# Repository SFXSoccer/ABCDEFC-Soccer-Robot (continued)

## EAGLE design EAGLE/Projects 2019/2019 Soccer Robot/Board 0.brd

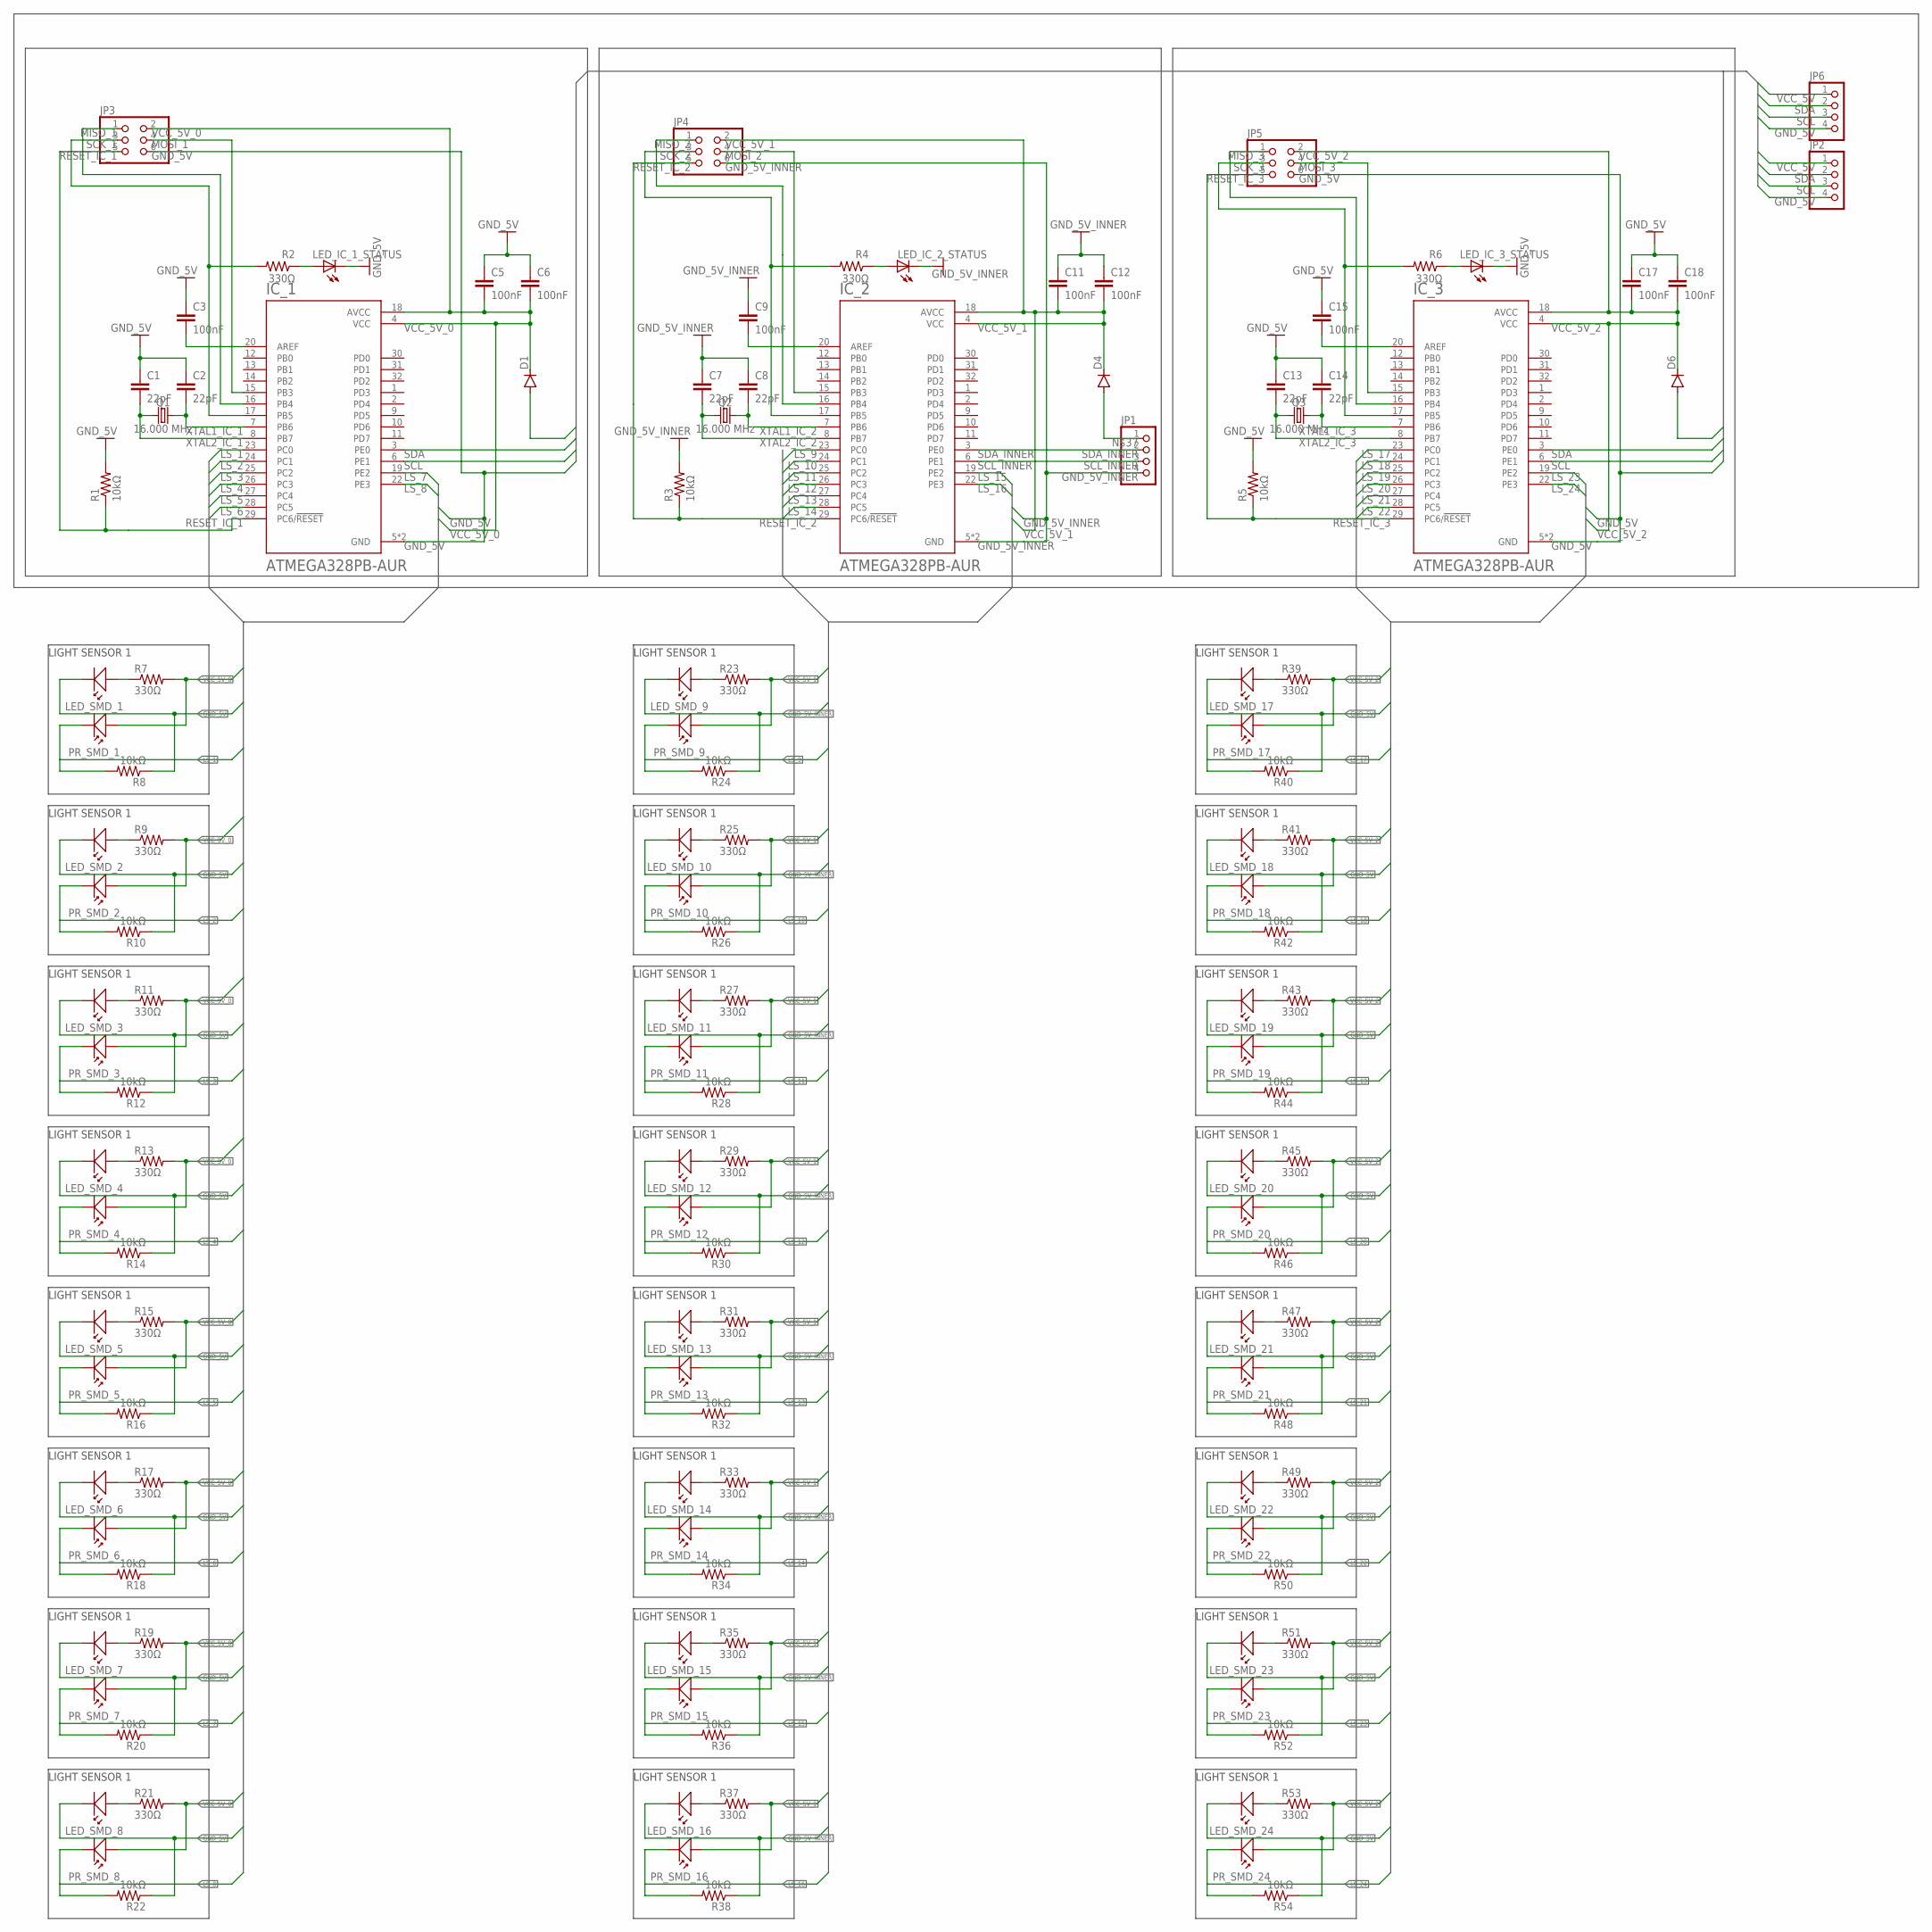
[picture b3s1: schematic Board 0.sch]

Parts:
C1, C2, C7, C8, C13, C14: 22pF; C1206
C3, C5, C6, C9, C11, C12, C15, C17, C18: 100nF; C1206
D1, D4, D6: DIODE-SOD123; SOD123
IC_1, IC_2, IC_3: ATMEGA328PB-AUR; QFP80P900X900X120-32N
JP1, JP2, JP6: PINHD-1X4_2.54-SMD; 1X04SMD
JP3, JP4, JP5: PINHD-2X3_2.54-SMD; 2X03SMD
LED_IC_1_STATUS, LED_IC_2_STATUS, LED_IC_3_STATUS: LEDP-LCC-2; P-LCC-2
LED_SMD_1, LED_SMD_2, LED_SMD_3, LED_SMD_4, LED_SMD_5, LED_SMD_6, LED_SMD_7, LED_SMD_8, LED_SMD_9, LED_SMD_10, LED_SMD_11, LED_SMD_12, LED_SMD_13, LED_SMD_14, LED_SMD_15, LED_SMD_16, LED_SMD_17, LED_SMD_18, LED_SMD_19, LED_SMD_20, LED_SMD_21, LED_SMD_22, LED_SMD_23, LED_SMD_24: SMD_LED_3MM
PR_SMD_1, PR_SMD_2, PR_SMD_3, PR_SMD_4, PR_SMD_5, PR_SMD_6, PR_SMD_7, PR_SMD_8, PR_SMD_9, PR_SMD_10, PR_SMD_11, PR_SMD_12, PR_SMD_13, PR_SMD_14, PR_SMD_15, PR_SMD_16, PR_SMD_17, PR_SMD_18, PR_SMD_19, PR_SMD_20, PR_SMD_21, PR_SMD_22, PR_SMD_23, PR_SMD_24: SMD_PHOTORESISTOR_5MM
Q1, Q2, Q3: 16.000 MHz; CRYSTAL-SMD-5X3.2-4PAD
R1, R3, R5, R8, R10, R12, R14, R16, R18, R20, R22, R24, R26, R28, R30, R32, R34, R36, R38, R40, R42, R44, R46, R48, R50, R52, R54: 10kΩ; R1206
R2, R4, R6, R7, R9, R11, R13, R15, R17, R19, R21, R23, R25, R27, R29, R31, R33, R35, R37, R39, R41, R43, R45, R47, R49, R51, R53: 330Ω; R1206

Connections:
GND_5V: C1.1, C2.1, C3.1, C5.1, C6.1, C13.1, C14.1, C15.1, C17.1, C18.1, IC_1.5 (GND), IC_1.21 (GND), IC_3.5 (GND), IC_3.21 (GND), JP2.4, JP3.6, JP5.6, JP6.4, LED_IC_1_STATUS.C, LED_IC_3_STATUS.C, LED_SMD_1.GND, LED_SMD_2.GND, LED_SMD_3.GND, LED_SMD_4.GND, LED_SMD_5.GND, LED_SMD_6.GND, LED_SMD_7.GND, LED_SMD_8.GND, LED_SMD_17.GND, LED_SMD_18.GND, LED_SMD_19.GND, LED_SMD_20.GND, LED_SMD_21.GND, LED_SMD_22.GND, LED_SMD_23.GND, LED_SMD_24.GND, R1.2, R5.2, R8.1, R10.1, R12.1, R14.1, R16.1, R18.1, R20.1, R22.1, R40.1, R42.1, R44.1, R46.1, R48.1, R50.1, R52.1, R54.1
GND_5V_INNER: C7.1, C8.1, C9.1, C11.1, C12.1, IC_2.5 (GND), IC_2.21 (GND), JP1.4, JP4.6, LED_IC_2_STATUS.C, LED_SMD_9.GND, LED_SMD_10.GND, LED_SMD_11.GND, LED_SMD_12.GND, LED_SMD_13.GND, LED_SMD_14.GND, LED_SMD_15.GND, LED_SMD_16.GND, R3.2, R24.1, R26.1, R28.1, R30.1, R32.1, R34.1, R36.1, R38.1
LS_1: IC_1.23 (PC0), PR_SMD_1.GND, R8.2
LS_2: IC_1.24 (PC1), PR_SMD_2.GND, R10.2
LS_3: IC_1.25 (PC2), PR_SMD_3.GND, R12.2
LS_4: IC_1.26 (PC3), PR_SMD_4.GND, R14.2
LS_5: IC_1.27 (PC4), PR_SMD_5.GND, R16.2
LS_6: IC_1.28 (PC5), PR_SMD_6.GND, R18.2
LS_7: IC_1.19 (PE2), PR_SMD_7.GND, R20.2
LS_8: IC_1.22 (PE3), PR_SMD_8.GND, R22.2
LS_9: IC_2.23 (PC0), PR_SMD_9.GND, R24.2
LS_10: IC_2.24 (PC1), PR_SMD_10.GND, R26.2
LS_11: IC_2.25 (PC2), PR_SMD_11.GND, R28.2
LS_12: IC_2.26 (PC3), PR_SMD_12.GND, R30.2
LS_13: IC_2.27 (PC4), PR_SMD_13.GND, R32.2
LS_14: IC_2.28 (PC5), PR_SMD_14.GND, R34.2
LS_15: IC_2.19 (PE2), PR_SMD_15.GND, R36.2
LS_16: IC_2.22 (PE3), PR_SMD_16.GND, R38.2
LS_17: IC_3.23 (PC0), PR_SMD_17.GND, R40.2
LS_18: IC_3.24 (PC1), PR_SMD_18.GND, R42.2
LS_19: IC_3.25 (PC2), PR_SMD_19.GND, R44.2
LS_20: IC_3.26 (PC3), PR_SMD_20.GND, R46.2
LS_21: IC_3.27 (PC4), PR_SMD_21.GND, R48.2
LS_22: IC_3.28 (PC5), PR_SMD_22.GND, R50.2
LS_23: IC_3.19 (PE2), PR_SMD_23.GND, R52.2
LS_24: IC_3.22 (PE3), PR_SMD_24.GND, R54.2
MISO_1: IC_1.16 (PB4), JP3.1
MISO_2: IC_2.16 (PB4), JP4.1
MISO_3: IC_3.16 (PB4), JP5.1
MOSI_1: IC_1.15 (PB3), JP3.4
MOSI_2: IC_2.15 (PB3), JP4.4
MOSI_3: IC_3.15 (PB3), JP5.4
unnamed: C3.2, IC_1.20 (AREF)
unnamed: LED_IC_1_STATUS.A, R2.1
unnamed: LED_SMD_2.VIN, R9.1
unnamed: C9.2, IC_2.20 (AREF)
unnamed: LED_IC_2_STATUS.A, R4.1
unnamed: LED_SMD_3.VIN, R11.1
unnamed: LED_SMD_4.VIN, R13.1
unnamed: C15.2, IC_3.20 (AREF)
unnamed: LED_IC_3_STATUS.A, R6.1
unnamed: LED_SMD_1.VIN, R7.1
unnamed: LED_SMD_5.VIN, R15.1
unnamed: LED_SMD_6.VIN, R17.1
unnamed: LED_SMD_7.VIN, R19.1
unnamed: LED_SMD_8.VIN, R21.1
unnamed: LED_SMD_9.VIN, R23.1
unnamed: LED_SMD_10.VIN, R25.1
unnamed: LED_SMD_11.VIN, R27.1
unnamed: LED_SMD_12.VIN, R29.1
unnamed: LED_SMD_13.VIN, R31.1
unnamed: LED_SMD_14.VIN, R33.1
unnamed: LED_SMD_15.VIN, R35.1
unnamed: LED_SMD_16.VIN, R37.1
unnamed: LED_SMD_17.VIN, R39.1
unnamed: LED_SMD_18.VIN, R41.1
unnamed: LED_SMD_19.VIN, R43.1
unnamed: LED_SMD_20.VIN, R45.1
unnamed: LED_SMD_21.VIN, R47.1
unnamed: LED_SMD_22.VIN, R49.1
unnamed: LED_SMD_23.VIN, R51.1
unnamed: LED_SMD_24.VIN, R53.1
unnamed: D4.A, JP1.1
RESET_IC_1: IC_1.29 (PC6/!RESET), JP3.5, R1.1
RESET_IC_2: IC_2.29 (PC6/!RESET), JP4.5, R3.1
RESET_IC_3: IC_3.29 (PC6/!RESET), JP5.5, R5.1
SCK_1: IC_1.17 (PB5), JP3.3, R2.2
SCK_2: IC_2.17 (PB5), JP4.3, R4.2
SCK_3: IC_3.17 (PB5), JP5.3, R6.2
SCL: IC_1.6 (PE1), IC_3.6 (PE1), JP2.3, JP6.3
SCL_INNER: IC_2.6 (PE1), JP1.3
SDA: IC_1.3 (PE0), IC_3.3 (PE0), JP2.2, JP6.2
SDA_INNER: IC_2.3 (PE0), JP1.2
VCC_5V: D1.A, D6.A, JP2.1, JP6.1
VCC_5V_0: C5.2, C6.2, D1.C, IC_1.4 (VCC), IC_1.18 (AVCC), JP3.2, PR_SMD_1.VIN, PR_SMD_2.VIN, PR_SMD_3.VIN, PR_SMD_4.VIN, PR_SMD_5.VIN, PR_SMD_6.VIN, PR_SMD_7.VIN, PR_SMD_8.VIN, R7.2, R9.2, R11.2, R13.2, R15.2, R17.2, R19.2, R21.2
VCC_5V_1: C11.2, C12.2, D4.C, IC_2.4 (VCC), IC_2.18 (AVCC), JP4.2, PR_SMD_9.VIN, PR_SMD_10.VIN, PR_SMD_11.VIN, PR_SMD_12.VIN, PR_SMD_13.VIN, PR_SMD_14.VIN, PR_SMD_15.VIN, PR_SMD_16.VIN, R23.2, R25.2, R27.2, R29.2, R31.2, R33.2, R35.2, R37.2
VCC_5V_2: C17.2, C18.2, D6.C, IC_3.4 (VCC), IC_3.18 (AVCC), JP5.2, PR_SMD_17.VIN, PR_SMD_18.VIN, PR_SMD_19.VIN, PR_SMD_20.VIN, PR_SMD_21.VIN, PR_SMD_22.VIN, PR_SMD_23.VIN, PR_SMD_24.VIN, R39.2, R41.2, R43.2, R45.2, R47.2, R49.2, R51.2, R53.2
XTAL1_IC_1: C2.2, IC_1.7 (PB6), Q1.3 (2)
XTAL1_IC_2: C8.2, IC_2.7 (PB6), Q2.3 (2)
XTAL1_IC_3: C14.2, IC_3.7 (PB6), Q3.3 (2)
XTAL2_IC_1: C1.2, IC_1.8 (PB7), Q1.1
XTAL2_IC_2: C7.2, IC_2.8 (PB7), Q2.1
XTAL2_IC_3: C13.2, IC_3.8 (PB7), Q3.1

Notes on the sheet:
LIGHT SENSOR 1

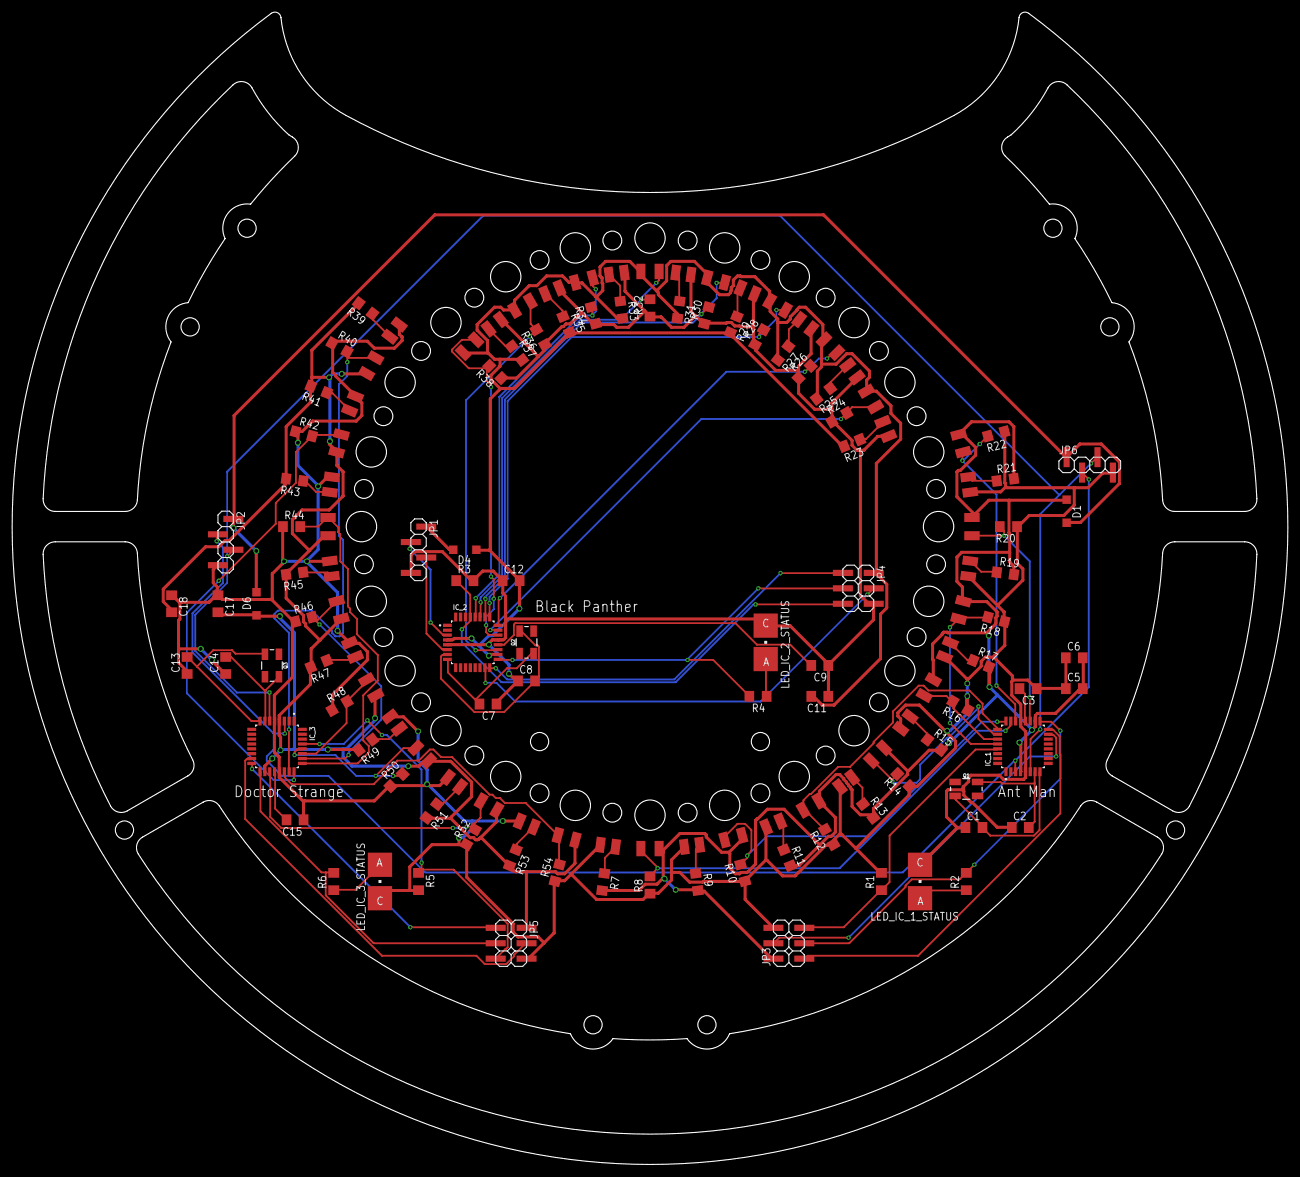
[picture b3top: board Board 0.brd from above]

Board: 2 copper layers, 210.0 x 189.7 mm, 135 parts (0 on the bottom side), 83 nets.

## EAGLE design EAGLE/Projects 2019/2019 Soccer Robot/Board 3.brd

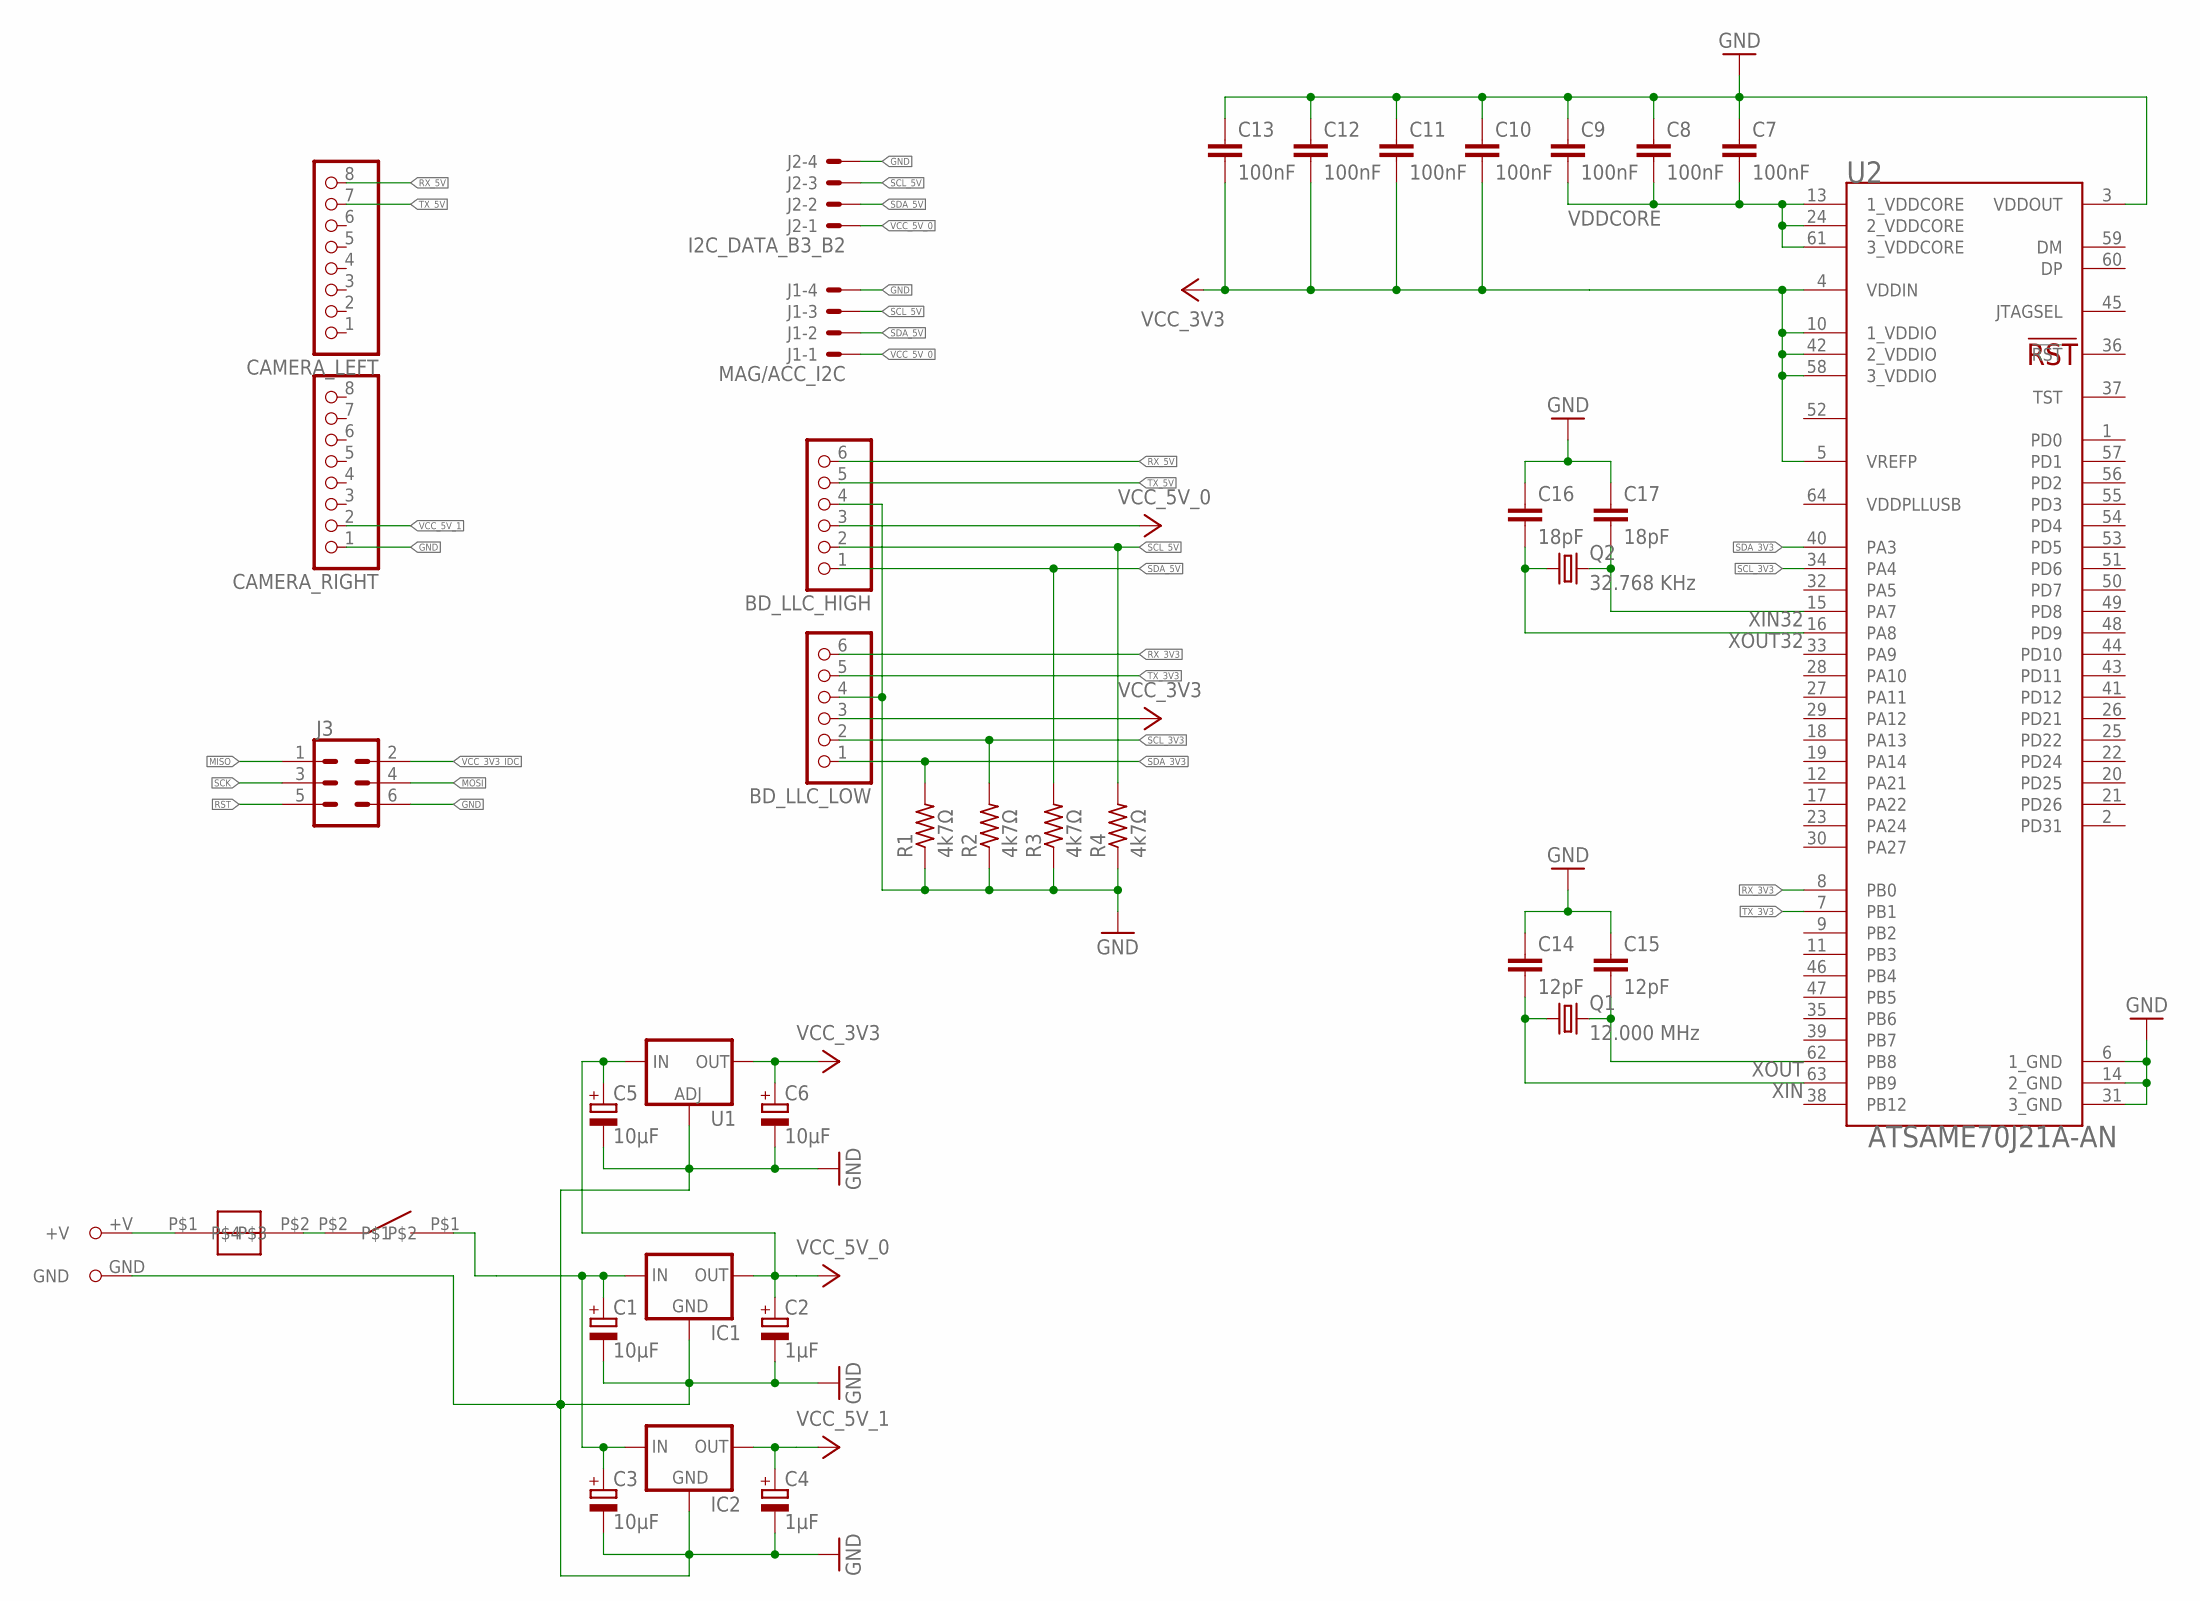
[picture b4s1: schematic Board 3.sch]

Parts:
BD_LLC_HIGH: PINHD-1X6; 1X06
BD_LLC_LOW: PINHD-1X6; 1X06
C1, C3, C5, C6: 10μF; E2-5
C2, C4: 1μF; E2-5
C7, C8, C9, C10, C11, C12, C13: 100nF; C050-024X044
C14, C15: 12pF; C050-024X044
C16, C17: 18pF; C050-024X044
CAMERA_LEFT: PINHD-1X8; 1X08
CAMERA_RIGHT: PINHD-1X8; 1X08
IC1, IC2: 78XXS
J1: MAG/ACC_I2C; 6410-04
J2: I2C_DATA_B3_B2; 6410-04
J3: CONN_03X2SHROUD; 2X3-SHROUDED
Q1: 12.000 MHz; HC49U-V
Q2: 32.768 KHz; TC26V
R1, R2, R3, R4: 4k7Ω; 0207/10
SICHERUNG1: SICHERUNG
U1: V_REG_LM1117SOT223; SOT223
U2: ATMEL_CORPORATION_ATSAME70J21A-ANATMEL_CORPORATIO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; ATMEL_CORPORATION_ATSAME70J21A-AN_0
U$1: XT60
U$17: SCHALTER

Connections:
+12V: C1.+, C3.+, IC1.IN, IC2.IN, U$17.P$1
GND: BD_LLC_HIGH.4, BD_LLC_LOW.4, C1.-, C2.-, C3.-, C4.-, C5.-, C6.-, C7.1, C8.1, C9.1, C10.1, C11.1, C12.1, C13.1, C14.1, C15.1, C16.1, C17.1, CAMERA_RIGHT.1, IC1.GND, IC2.GND, J1.4, J2.4, J3.6, R1.1, R2.1, R3.1, R4.1, U1.1 (ADJ), U2.3 (VDDOUT), U2.6 (1_GND), U2.14 (2_GND), U2.31 (3_GND), U$1.GND
MISO: J3.1
MOSI: J3.4
unnamed: SICHERUNG1.P$1, U$1.+V
unnamed: SICHERUNG1.P$2, U$17.P$2
RST: J3.5
RX_3V3: BD_LLC_LOW.6, U2.8 (PB0)
RX_5V: BD_LLC_HIGH.6, CAMERA_LEFT.8
SCK: J3.3
SCL_3V3: BD_LLC_LOW.2, R2.2, U2.34 (PA4)
SCL_5V: BD_LLC_HIGH.2, J1.3, J2.3, R4.2
SDA_3V3: BD_LLC_LOW.1, R1.2, U2.40 (PA3)
SDA_5V: BD_LLC_HIGH.1, J1.2, J2.2, R3.2
TX_3V3: BD_LLC_LOW.5, U2.7 (PB1)
TX_5V: BD_LLC_HIGH.5, CAMERA_LEFT.7
VCC_3V3: BD_LLC_LOW.3, C6.+, C10.2, C11.2, C12.2, C13.2, U1.2 (OUT), U1.4 (OUT), U2.4 (VDDIN), U2.5 (VREFP), U2.10 (1_VDDIO), U2.42 (2_VDDIO), U2.58 (3_VDDIO)
VCC_3V3_IDC: J3.2
VCC_5V_0: BD_LLC_HIGH.3, C2.+, C5.+, IC1.OUT, J1.1, J2.1, U1.3 (IN)
VCC_5V_1: C4.+, CAMERA_RIGHT.2, IC2.OUT
VDDCORE: C7.2, C8.2, C9.2, U2.13 (1_VDDCORE), U2.24 (2_VDDCORE), U2.61 (3_VDDCORE)
XIN: C14.2, Q1.1, U2.63 (PB9)
XIN32: C17.2, Q2.2, U2.15 (PA7)
XOUT: C15.2, Q1.2, U2.62 (PB8)
XOUT32: C16.2, Q2.1, U2.16 (PA8)

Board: 2 copper layers, 37 parts (1 on the bottom side), 20 nets, no tracks yet.

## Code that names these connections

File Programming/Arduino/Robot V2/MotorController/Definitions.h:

#pragma once

#ifndef _AVR_ATMEGA328PB_H_INCLUDED
#error "Wrong board selected for this program, please select an ATmega328PB"
#endif

#define GUARDIANS_OF_THE_GALAXY

#pragma region General

#ifdef GUARDIANS_OF_THE_GALAXY
#define	ADDRESS					0x05
#endif

#define DELAY_LIGHTGATE			0
#define DELAY_BALL_DETECTED		500

#define DIR_FORWARD				0x1
#define DIR_REVERSE				0x0

#define MOTOR_1_ANGLE			30
#define MOTOR_2_ANGLE			150
#define MOTOR_3_ANGLE			270
#define MOTOR_4_ANGLE			0

#pragma endregion

#pragma region Commands

#define CMD_MOTOR				0x15
#define CMD_LIGHTGATE			0x16

#pragma endregion

#pragma region Pins

#define LED_STATUS				LED_BUILTIN

#define PIN_LIGHTGATE_PWR		19
#define PIN_LIGHTGATE			A4

#define PIN_MOTOR_1_SPEED		9
#define PIN_MOTOR_1_DIRECTION	15
#define PIN_MOTOR_1_BRAKE		14

#define PIN_MOTOR_2_SPEED		10
#define PIN_MOTOR_2_DIRECTION	17
#define PIN_MOTOR_2_BRAKE		16

#define PIN_MOTOR_3_SPEED		11
#define PIN_MOTOR_3_DIRECTION	13
#define PIN_MOTOR_3_BRAKE		12

#define PIN_MOTOR_4_SPEED		3
#define PIN_MOTOR_4_DIRECTION	4
#define PIN_MOTOR_4_BRAKE		2
#pragma endregion

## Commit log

2019-07-01 Initial Project Push
2019-07-01 Inventor Files
2019-07-02 A few fixes
2019-07-03 Camera
2019-07-04 Many chnages
2019-07-04 Fixed a bug with the motors
2019-07-05 Made Changes
2019-07-12 Soccer Robot Program
